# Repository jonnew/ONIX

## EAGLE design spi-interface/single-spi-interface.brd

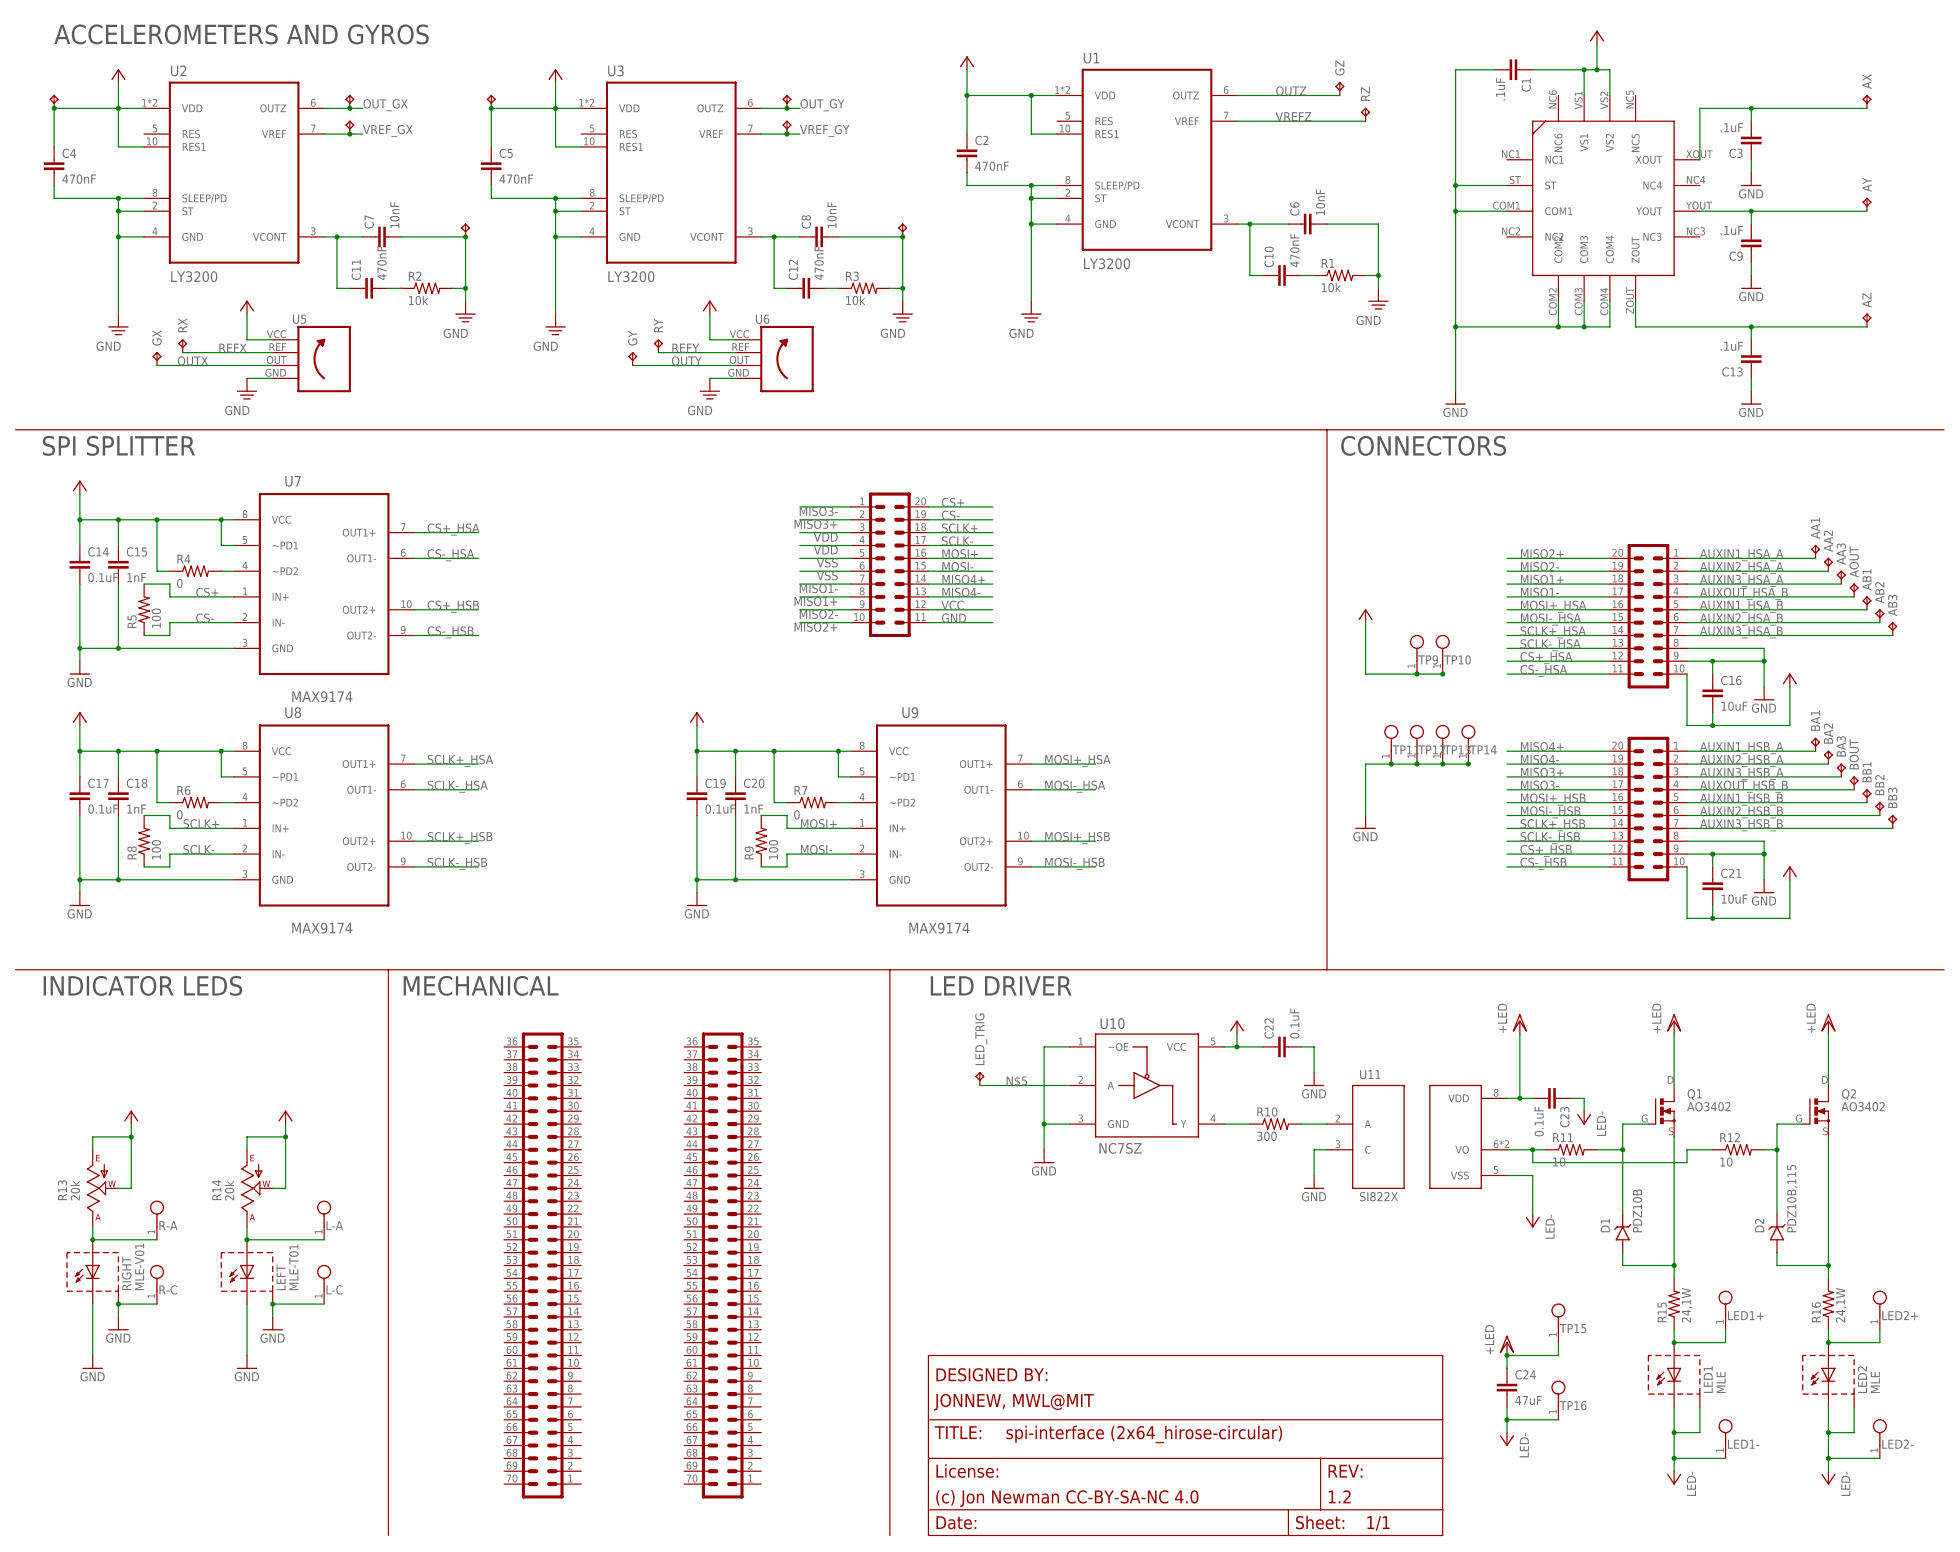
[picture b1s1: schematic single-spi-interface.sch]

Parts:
AA1, AA2, AA3: TP_0.5MM; TESTPOINT_0.5MM
AB1, AB2, AB3: TP_0.5MM; TESTPOINT_0.5MM
AOUT: TP_0.5MM; TESTPOINT_0.5MM
AX: TP_0.5MM; TESTPOINT_0.5MM
AY: TP_0.5MM; TESTPOINT_0.5MM
AZ: TP_0.5MM; TESTPOINT_0.5MM
BA1, BA2, BA3: TP_0.5MM; TESTPOINT_0.5MM
BB1, BB2, BB3: TP_0.5MM; TESTPOINT_0.5MM
BOUT: TP_0.5MM; TESTPOINT_0.5MM
C1: .1uF; 0402
C2, C4, C5, C10, C11, C12: 470nF; 0201
C3, C9, C13: .1uF; 0201
C6, C7, C8: 10nF; 0201
C14, C17, C19, C22, C23: 0.1uF; 0402
C15, C18, C20: 1nF; 0201
C16, C21: 10uF; 0805
C24: 47uF; 1206
D1: PDZ10B; SOD-323
D2: PDZ10B,115; SOD-323
DIO_HSA: PINHD-2X10_DF40-20REC; DF40-20REC
DIO_HSB: PINHD-2X10_DF40-20REC; DF40-20REC
GX: TP_0.5MM; TESTPOINT_0.5MM
GY: TP_0.5MM; TESTPOINT_0.5MM
GZ: TP_0.5MM; TESTPOINT_0.5MM
L-A: TESTPOINT_SMALL
L-C: TESTPOINT_SMALL
LED1, LED2: MLE; LED-MLE
LED1+, LED1-, LED2+, LED2-: TESTPOINT_SMALL
LED_TRIG: TP_0.5MM; TESTPOINT_0.5MM
LEFT: MLE-T01; LED-MLE
MECH_E0B: PINHD-2X35_DF40REC; DF40-70REC
MECH_W0B: PINHD-2X35_DF40REC; DF40-70REC
Q1, Q2: AO3402; SOT23-GSD
R1, R2, R3: 10k; 0201
R4, R6, R7: 0; 0201
R5, R8, R9: 100; 0201
R10: 300; 0402
R11, R12: 10; 0402
R13, R14: 20k; SM-42/43W
R15, R16: 24,1W; 0805
R-A: TESTPOINT_SMALL
R-C: TESTPOINT_SMALL
RIGHT: MLE-V01; LED-MLE
RX: TP_0.5MM; TESTPOINT_0.5MM
RY: TP_0.5MM; TESTPOINT_0.5MM
RZ: TP_0.5MM; TESTPOINT_0.5MM
TETHER: T1M-10-T-DV
TP1, TP2, TP3, TP4, TP5, TP6, TP7, TP8: TPTP08SQ; TP08SQ
TP9, TP10, TP11, TP12, TP13, TP14, TP15, TP16: TESTPOINT_SMALL
U1, U2, U3: LY3200; LGA-10-COMPACT
U4: ADXL335
U5, U6: LY3200-VERT-MODULE
U7, U8, U9: MAX9174; 10-UMAX
U10: NC7SZ; SOT-23-5
U11: SI822X; SOIC127P500X400-8N

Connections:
AUXIN1_HSA_A: AA1.1, DIO_HSA.1
AUXIN1_HSA_B: AB1.1, DIO_HSA.5
AUXIN1_HSB_A: BA1.1, DIO_HSB.1
AUXIN1_HSB_B: BB1.1, DIO_HSB.5
AUXIN2_HSA_A: AA2.1, DIO_HSA.2
AUXIN2_HSA_B: AB2.1, DIO_HSA.6
AUXIN2_HSB_A: BA2.1, DIO_HSB.2
AUXIN2_HSB_B: BB2.1, DIO_HSB.6
AUXIN3_HSA_A: AA3.1, DIO_HSA.3
AUXIN3_HSA_B: AB3.1, DIO_HSA.7
AUXIN3_HSB_A: BA3.1, DIO_HSB.3
AUXIN3_HSB_B: BB3.1, DIO_HSB.7
AUXOUT_HSA_B: AOUT.1, DIO_HSA.4
AUXOUT_HSB_B: BOUT.1, DIO_HSB.4
CS+: R5.2, TETHER.20, U7.1 (IN+)
CS+_HSA: DIO_HSA.12, U7.7 (OUT1+)
CS+_HSB: DIO_HSB.12, U7.10 (OUT2+)
CS-: R5.1, TETHER.19, U7.2 (IN-)
CS-_HSA: DIO_HSA.11, U7.6 (OUT1-)
CS-_HSB: DIO_HSB.11, U7.9 (OUT2-)
GND: C1.2, C2.2, C3.1, C4.2, C5.2, C6.2, C7.2, C8.2, C9.1, C13.1, C14.2, C15.2, C16.1, C17.2, C18.2, C19.2, C20.2, C21.1, C22.2, DIO_HSA.8, DIO_HSA.9, DIO_HSB.8, DIO_HSB.9, L-C.1, LEFT.C1 (C), LEFT.C2 (C), LEFT.HS (BODY), R1.2, R2.2, R3.2, R-C.1, RIGHT.C1 (C), RIGHT.C2 (C), RIGHT.HS (BODY), TETHER.11, TP7.TP, TP8.TP, TP11.1, TP12.1, TP13.1, TP14.1, U1.2 (ST), U1.4 (GND), U1.8 (SLEEP/PD), U2.2 (ST), U2.4 (GND), U2.8 (SLEEP/PD), U3.2 (ST), U3.4 (GND), U3.8 (SLEEP/PD), U4.COM1, U4.COM2, U4.COM3, U4.COM4, U4.ST, U5.GND, U6.GND, U7.3 (GND), U8.3 (GND), U9.3 (GND), U10.1 (~OE), U10.3 (GND), U11.3 (C)
MISO1+: DIO_HSA.18, TETHER.8
MISO1-: DIO_HSA.17, TETHER.7
MISO2+: DIO_HSA.20, TETHER.10
MISO2-: DIO_HSA.19, TETHER.9
MISO3+: DIO_HSB.18, TETHER.2
MISO3-: DIO_HSB.17, TETHER.1
MISO4+: DIO_HSB.20, TETHER.14
MISO4-: DIO_HSB.19, TETHER.13
MOSI+: R9.2, TETHER.16, U9.1 (IN+)
MOSI+_HSA: DIO_HSA.16, U9.7 (OUT1+)
MOSI+_HSB: DIO_HSB.16, U9.10 (OUT2+)
MOSI-: R9.1, TETHER.15, U9.2 (IN-)
MOSI-_HSA: DIO_HSA.15, U9.6 (OUT1-)
MOSI-_HSB: DIO_HSB.15, U9.9 (OUT2-)
unnamed: R10.2, U11.2 (A)
unnamed: C7.1, C11.1, U2.3 (VCONT)
unnamed: LED1.A1 (A), LED1.A2 (A), LED1+.1, R15.1
unnamed: D1.A, Q1.S, R15.2
unnamed: LED_TRIG.1, U10.2 (A)
unnamed: R10.1, U10.4 (Y)
unnamed: D2.C, Q2.G, R12.2
unnamed: C11.2, R2.1
unnamed: R13.1 (A), R-A.1, RIGHT.A1 (A), RIGHT.A2 (A)
unnamed: C8.1, C12.1, U3.3 (VCONT)
unnamed: D2.A, Q2.S, R16.2
unnamed: LED2.A1 (A), LED2.A2 (A), LED2+.1, R16.1
unnamed: L-A.1, LEFT.A1 (A), LEFT.A2 (A), R14.1 (A)
unnamed: C12.2, R3.1
unnamed: C6.1, C10.1, U1.3 (VCONT)
unnamed: C10.2, R1.1
unnamed: R4.2, U7.4 (~PD2)
unnamed: R7.2, U9.4 (~PD2)
unnamed: R6.2, U8.4 (~PD2)
unnamed: D1.C, Q1.G, R11.2
unnamed: R11.1, R12.1, U11.6 (VO), U11.7 (VO)
OUTX: GX.1, U5.OUT
OUTY: GY.1, U6.OUT
OUTZ: GZ.1, U1.6 (OUTZ)
OUT_GX: TP2.TP, U2.6 (OUTZ)
OUT_GY: TP4.TP, U3.6 (OUTZ)
REFX: RX.1, U5.REF
REFY: RY.1, U6.REF
SCLK+: R8.2, TETHER.18, U8.1 (IN+)
SCLK+_HSA: DIO_HSA.14, U8.7 (OUT1+)
SCLK+_HSB: DIO_HSB.14, U8.10 (OUT2+)
SCLK-: R8.1, TETHER.17, U8.2 (IN-)
SCLK-_HSA: DIO_HSA.13, U8.6 (OUT1-)
SCLK-_HSB: DIO_HSB.13, U8.9 (OUT2-)
VCC: C1.1, C2.1, C4.1, C5.1, C14.1, C15.1, C16.2, C17.1, C18.1, C19.1, C20.1, C21.2, C22.1, DIO_HSA.10, DIO_HSB.10, R4.1, R6.1, R7.1, R13.2 (W), R13.3 (E), R14.2 (W), R14.3 (E), TETHER.12, TP1.TP, TP3.TP, TP9.1, TP10.1, U1.1 (VDD), U1.9 (VDD), U1.10 (RES1), U2.1 (VDD), U2.9 (VDD), U2.10 (RES1), U3.1 (VDD), U3.9 (VDD), U3.10 (RES1), U4.VS1, U4.VS2, U5.VCC, U6.VCC, U7.5 (~PD1), U7.8 (VCC), U8.5 (~PD1), U8.8 (VCC), U9.5 (~PD1), U9.8 (VCC), U10.5 (VCC)
VDD: C23.2, C24.1, Q1.D, Q2.D, TETHER.3, TETHER.4, TP15.1, U11.8 (VDD)
VREFZ: RZ.1, U1.7 (VREF)
VREF_GX: TP5.TP, U2.7 (VREF)
VREF_GY: TP6.TP, U3.7 (VREF)
VSS: C23.1, C24.2, LED1.C1 (C), LED1.C2 (C), LED1.HS (BODY), LED1-.1, LED2.C1 (C), LED2.C2 (C), LED2.HS (BODY), LED2-.1, TETHER.5, TETHER.6, TP16.1, U11.5 (VSS)
XOUT1: AX.1, C3.2, U4.XOUT
YOUT1: AY.1, C9.2, U4.YOUT
ZOUT1: AZ.1, C13.2, U4.ZOUT

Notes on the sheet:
SPI SPLITTER
MECHANICAL
LED DRIVER
CONNECTORS
INDICATOR LEDS
ACCELEROMETERS AND GYROS

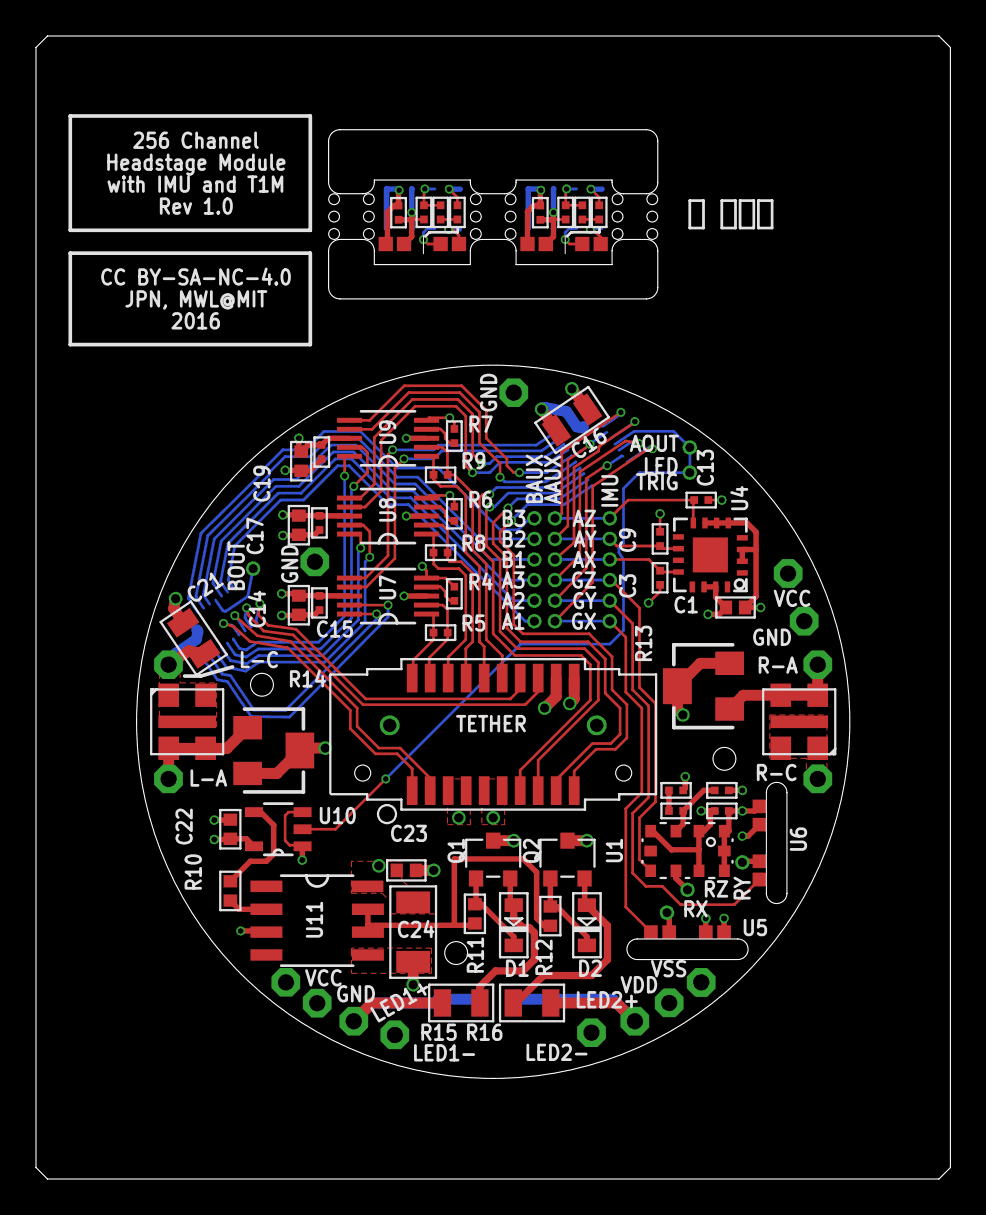
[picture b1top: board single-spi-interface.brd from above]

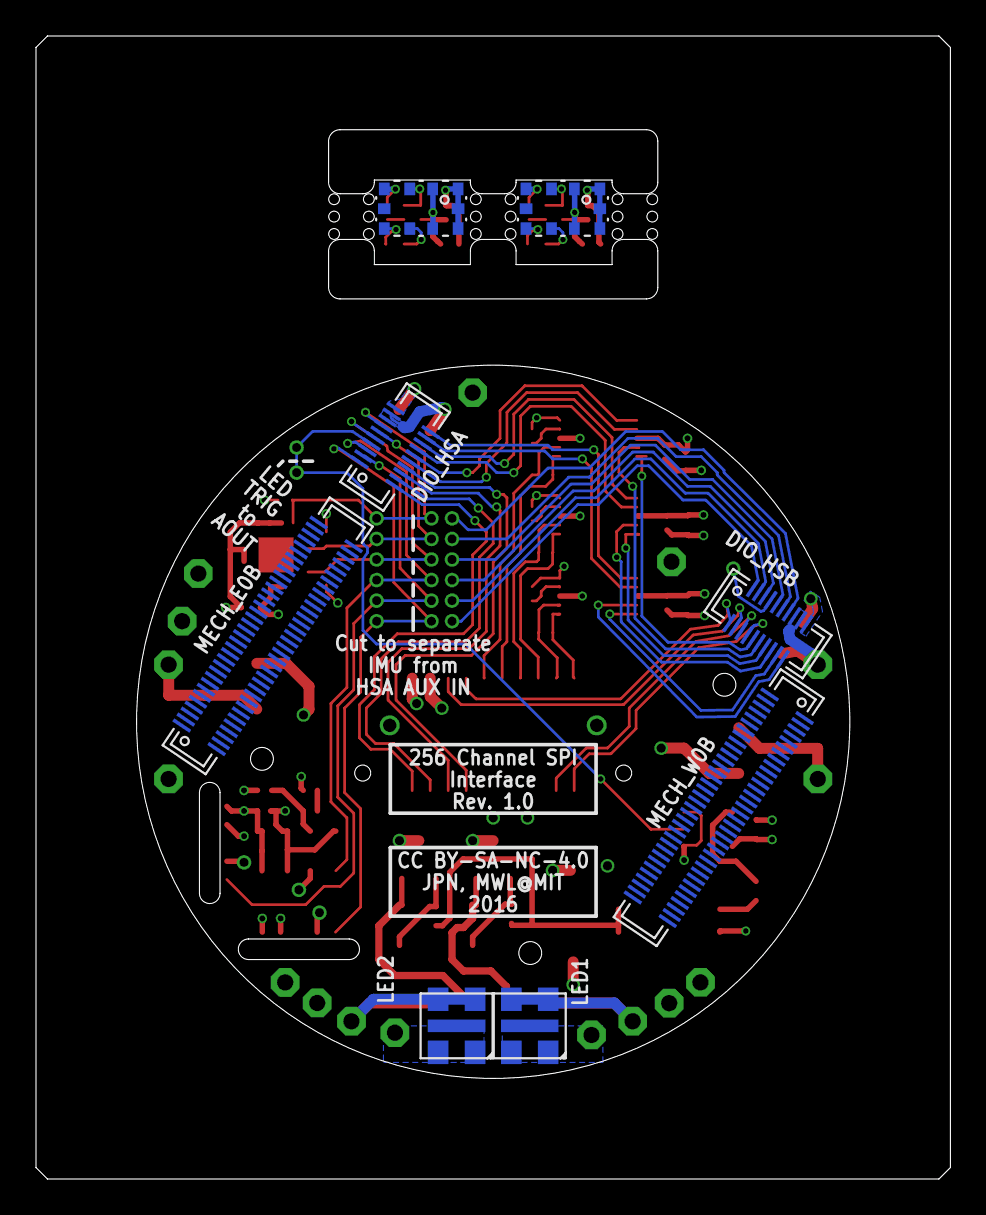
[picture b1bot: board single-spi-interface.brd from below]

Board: 4 copper layers, 50.8 x 63.5 mm, 112 parts (8 on the bottom side), 78 nets.

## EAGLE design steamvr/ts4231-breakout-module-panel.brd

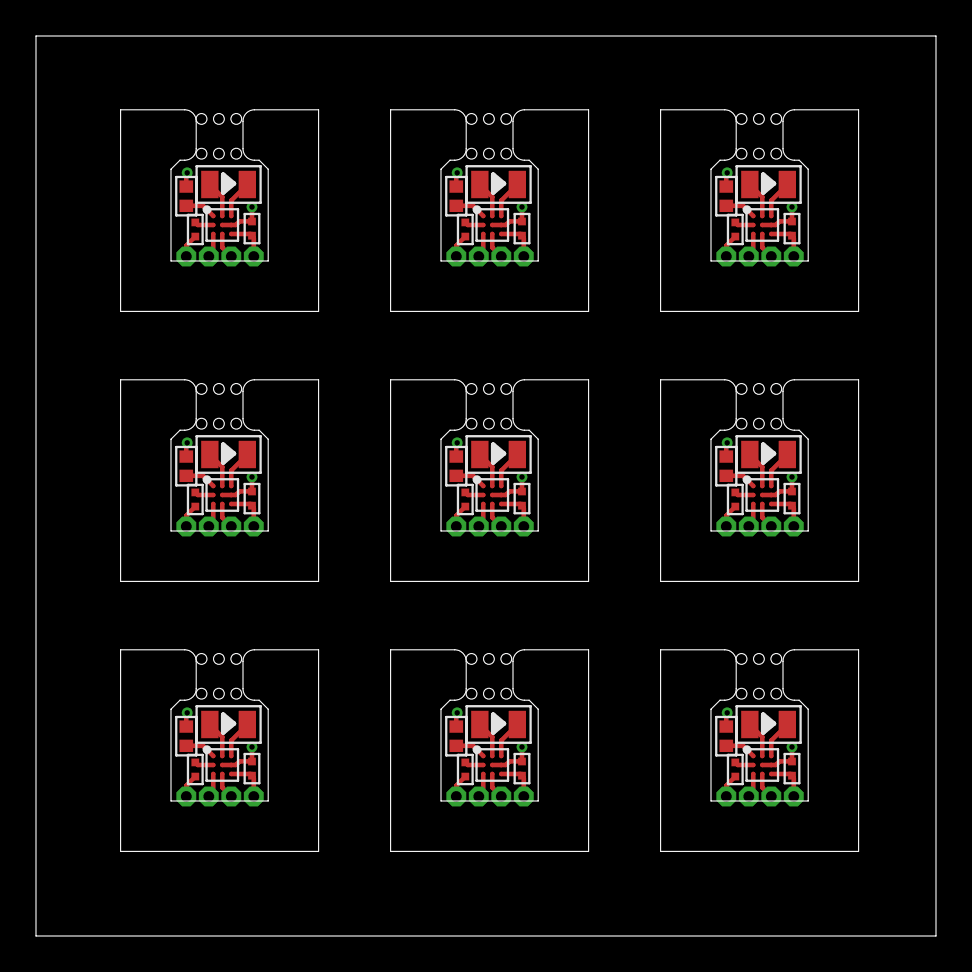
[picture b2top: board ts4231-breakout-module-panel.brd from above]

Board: 2 copper layers, 50.0 x 50.0 mm, 81 parts (0 on the bottom side), 72 nets.

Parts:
C1, C3, C5, C7, C9, C11, C13, C15, C17: 1uF; 0402
C2, C4, C6, C8, C10, C12, C14, C16, C18: 0.1uF; 0201
D, D3, D5, D7, D9, D11, D13, D15, D17: TP23MIL
D1, D2, D4, D6, D8, D10, D12, D14, D16: 0805
E, E1, E2, E3, E4, E5, E6, E7, E8: TP23MIL
GND, GND1, GND2, GND3, GND4, GND5, GND6, GND7, GND8: TP23MIL
R1, R2, R3, R4, R5, R6, R7, R8, R9: 15k; 0201
U1, U2, U3, U4, U5, U6, U7, U8, U9: TS4231; WLCSP3X3
VDD, VDD1, VDD2, VDD3, VDD4, VDD5, VDD6, VDD7, VDD8: TP23MIL

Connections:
GND: C1.2, C2.2, GND.P$1, R1.1, U1.B2, U1.B3
GND1: C3.2, C4.2, GND1.P$1, R2.1, U2.B2, U2.B3
GND2: C5.2, C6.2, GND2.P$1, R3.1, U3.B2, U3.B3
GND3: C7.2, C8.2, GND3.P$1, R4.1, U4.B2, U4.B3
GND4: C9.2, C10.2, GND4.P$1, R5.1, U5.B2, U5.B3
GND5: C11.2, C12.2, GND5.P$1, R6.1, U6.B2, U6.B3
GND6: C13.2, C14.2, GND6.P$1, R7.1, U7.B2, U7.B3
GND7: C15.2, C16.2, GND7.P$1, R8.1, U8.B2, U8.B3
GND8: C17.2, C18.2, GND8.P$1, R9.1, U9.B2, U9.B3
unnamed: D.P$1, U1.C1
unnamed: E.P$1, U1.C2
unnamed: D3.P$1, U2.C1
unnamed: D1.2, U1.A3
unnamed: D1.1, U1.A2
unnamed: R1.2, U1.B1
unnamed: C1.1, U1.A1
unnamed: E1.P$1, U2.C2
unnamed: D2.2, U2.A3
unnamed: D2.1, U2.A2
unnamed: R2.2, U2.B1
unnamed: C3.1, U2.A1
unnamed: D5.P$1, U3.C1
unnamed: E2.P$1, U3.C2
unnamed: D4.2, U3.A3
unnamed: D4.1, U3.A2
unnamed: R3.2, U3.B1
unnamed: C5.1, U3.A1
unnamed: D7.P$1, U4.C1
unnamed: E3.P$1, U4.C2
unnamed: D6.2, U4.A3
unnamed: D6.1, U4.A2
unnamed: R4.2, U4.B1
unnamed: C7.1, U4.A1
unnamed: D9.P$1, U5.C1
unnamed: E4.P$1, U5.C2
unnamed: D8.2, U5.A3
unnamed: D8.1, U5.A2
unnamed: R5.2, U5.B1
unnamed: C9.1, U5.A1
unnamed: D11.P$1, U6.C1
unnamed: E5.P$1, U6.C2
unnamed: D10.2, U6.A3
unnamed: D10.1, U6.A2
unnamed: R6.2, U6.B1
unnamed: C11.1, U6.A1
unnamed: D13.P$1, U7.C1
unnamed: E6.P$1, U7.C2
unnamed: D12.2, U7.A3
unnamed: D12.1, U7.A2
unnamed: R7.2, U7.B1
unnamed: C13.1, U7.A1
unnamed: D15.P$1, U8.C1
unnamed: E7.P$1, U8.C2
unnamed: D14.2, U8.A3
unnamed: D14.1, U8.A2
unnamed: R8.2, U8.B1
unnamed: C15.1, U8.A1
unnamed: D17.P$1, U9.C1
unnamed: E8.P$1, U9.C2
unnamed: D16.2, U9.A3
unnamed: D16.1, U9.A2
unnamed: R9.2, U9.B1
unnamed: C17.1, U9.A1
VDD: C2.1, U1.C3, VDD.P$1
VDD1: C4.1, U2.C3, VDD1.P$1
VDD2: C6.1, U3.C3, VDD2.P$1
VDD3: C8.1, U4.C3, VDD3.P$1
VDD4: C10.1, U5.C3, VDD4.P$1
VDD5: C12.1, U6.C3, VDD5.P$1
VDD6: C14.1, U7.C3, VDD6.P$1
VDD7: C16.1, U8.C3, VDD7.P$1
VDD8: C18.1, U9.C3, VDD8.P$1

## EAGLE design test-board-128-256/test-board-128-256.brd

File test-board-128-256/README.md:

# test-board-128-256
Test board for [headstage-256](../headstage-256). Allows injecting simulated
biopotentials into headstage modules via a selectable passive attenuator.
Provides LEDs and simulated electrical loads for optical and electrical
stimulation.

## Gerber Files
{% include gerber_layers.md %}

## Bill of Materials
The BOM is located on [this google
sheet](https://docs.google.com/spreadsheets/d/1F-KWcdvH_63iXjZf0cgCfDiFX6XXW3qw6rlR8DZrFpQ/edit#gid=1193719109)

## Pinout
The EIB pinout (ADC input mapping, stimulation connections, etc) is located on
[this google
sheet](https://docs.google.com/spreadsheets/d/11wRDYOqHN5lPb03yUdfXfK0zvaDYsVetplaNK-R90Gg/edit#gid=663991061)

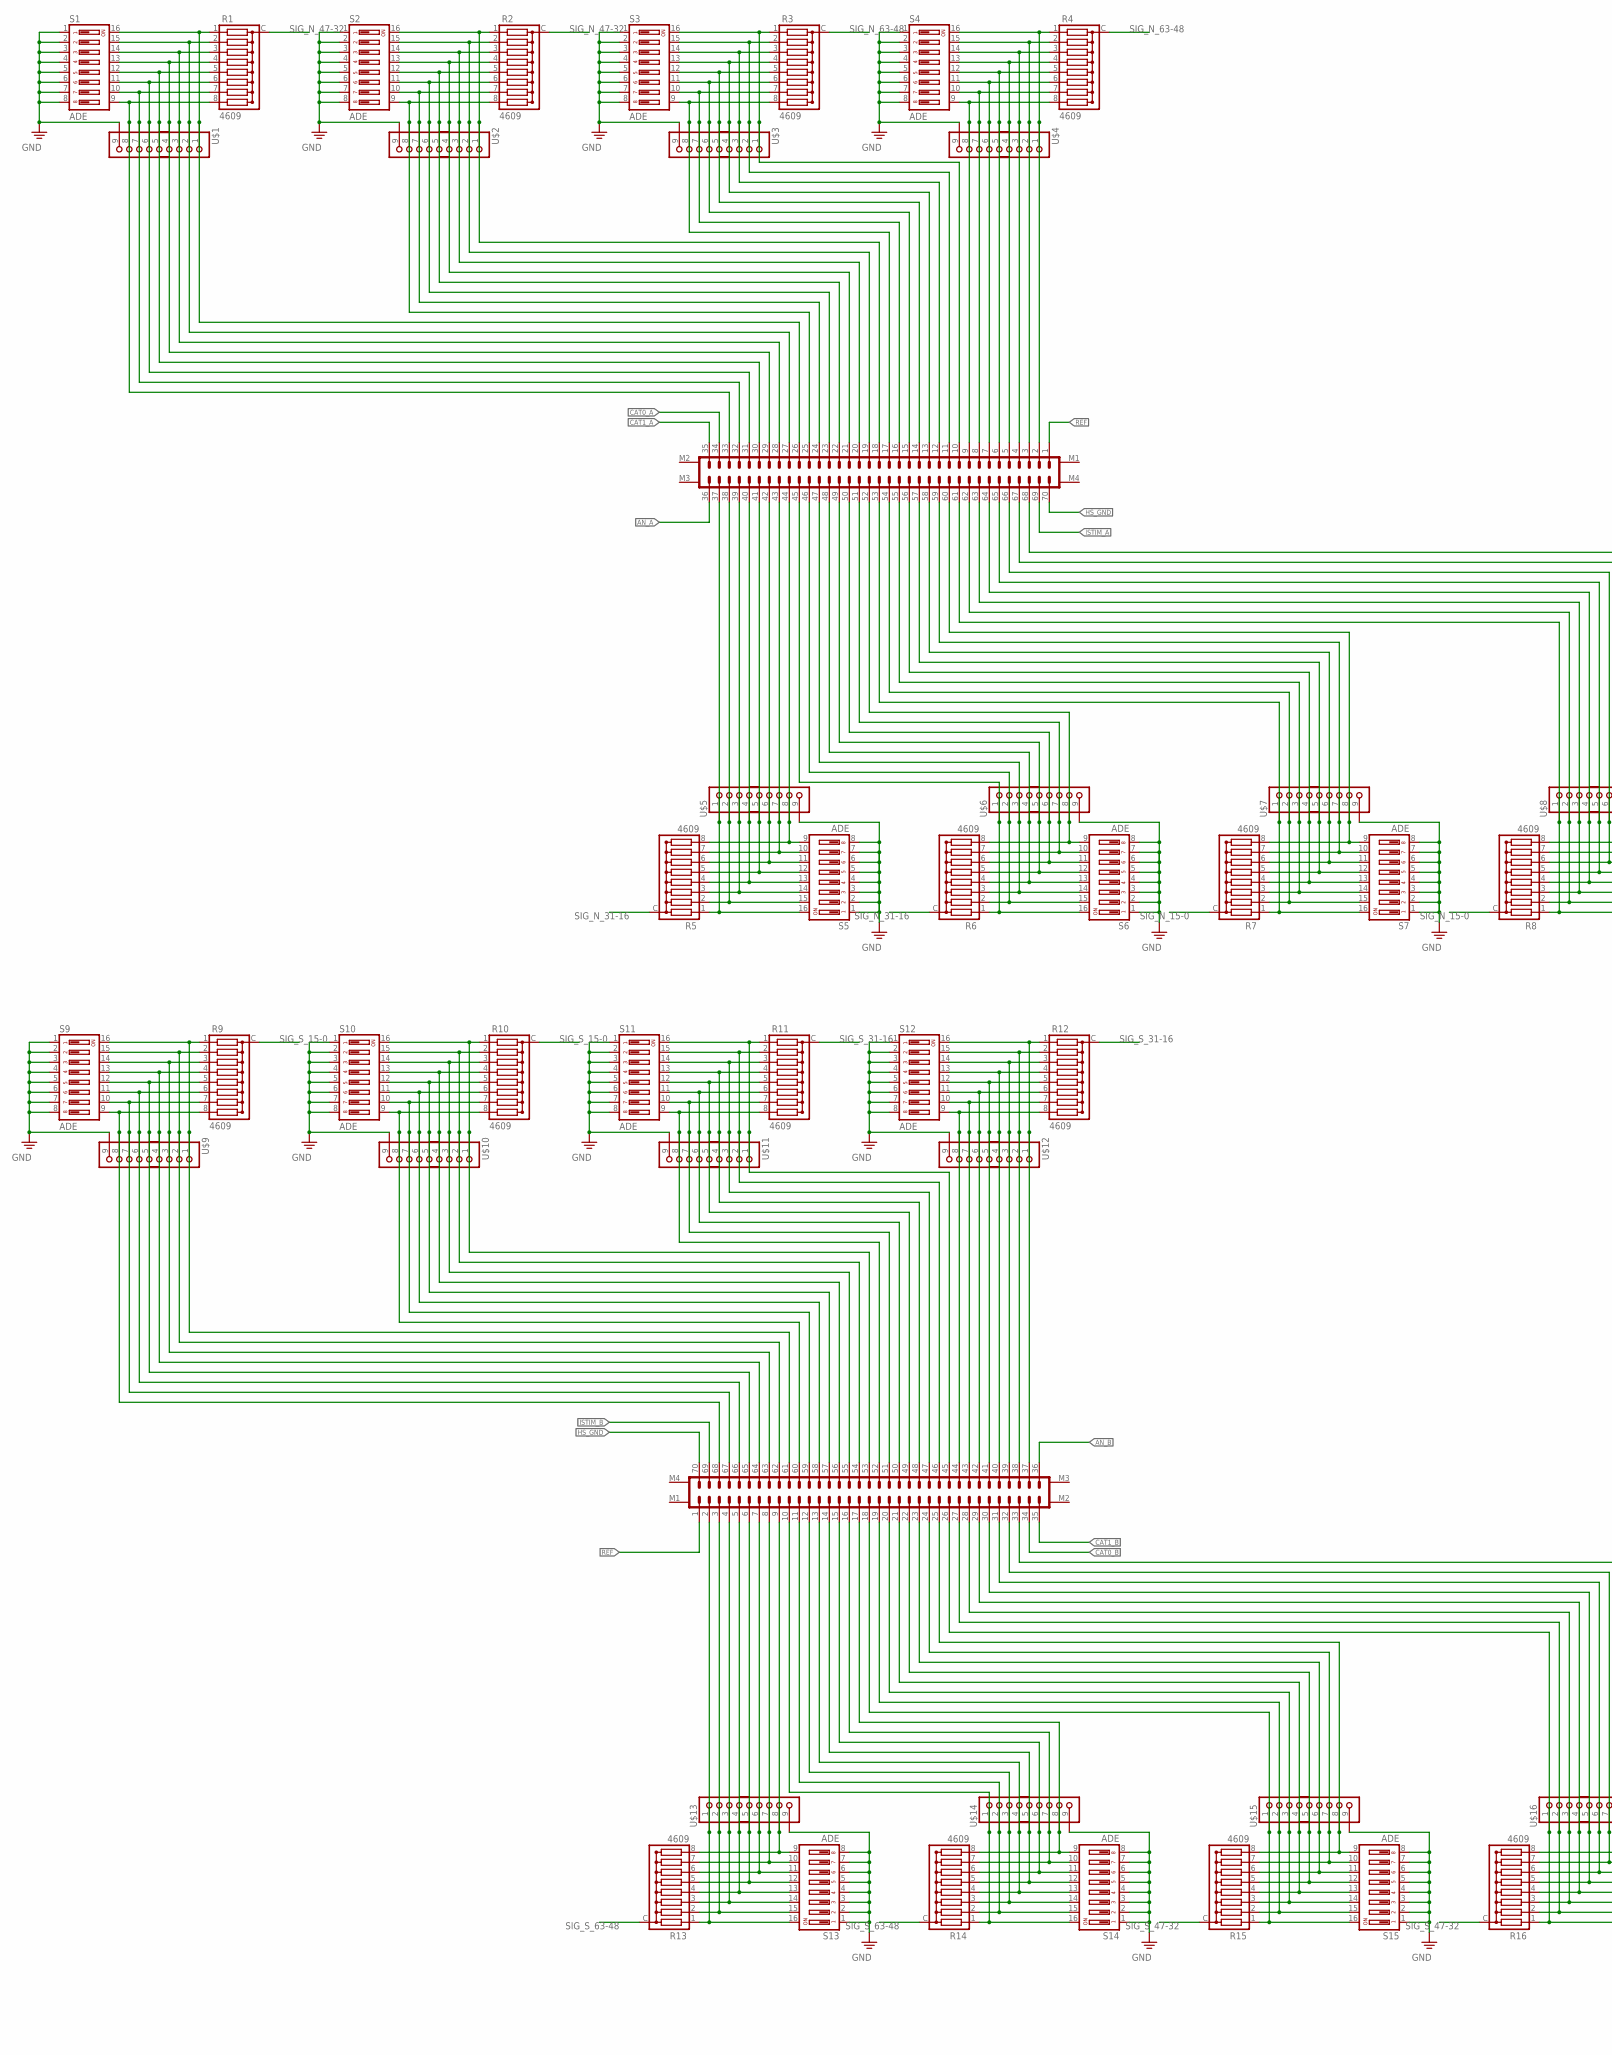
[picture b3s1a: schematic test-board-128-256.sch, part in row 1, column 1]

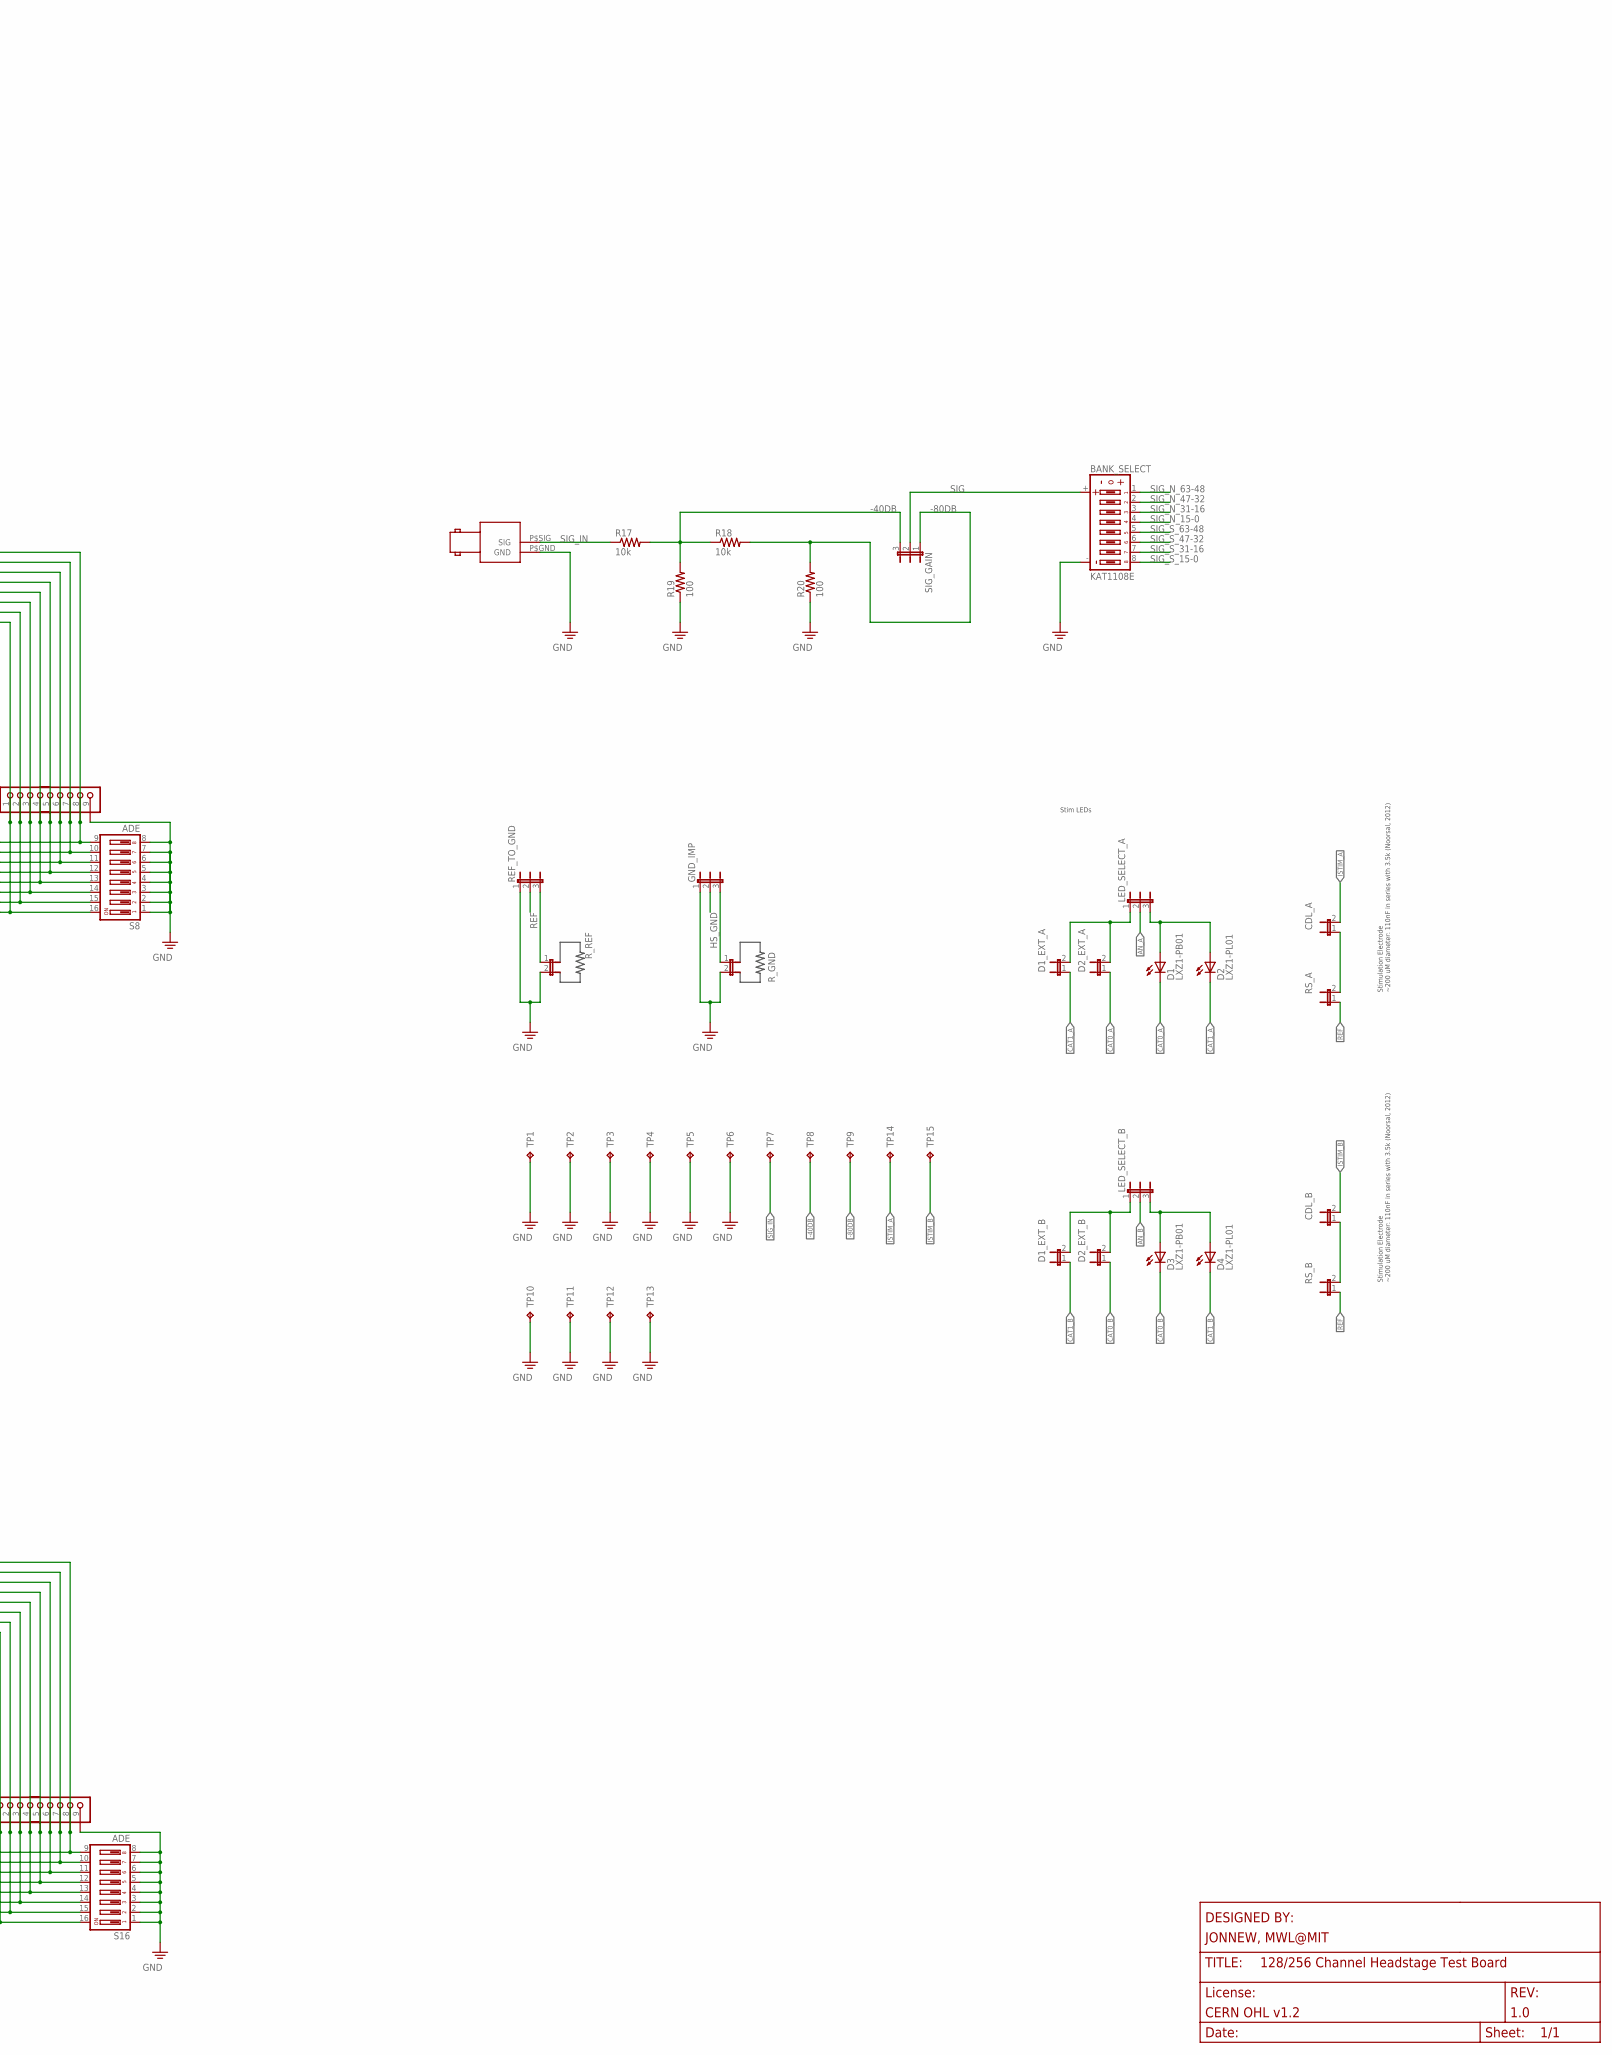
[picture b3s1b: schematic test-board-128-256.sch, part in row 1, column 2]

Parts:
A-OR-D: DF40HEAD; DF40-70HEAD
B-OR-C: DF40HEAD; DF40-70HEAD
BANK_SELECT: KAT1108E; 206-124_DIP8-SPDT
CDL_A: JP2E_THRU-HOLE; JP2
CDL_B: JP2E_THRU-HOLE; JP2
D1, D3: LXZ1-PB01; LXZ1
D1_EXT_A, D1_EXT_B, D2_EXT_A, D2_EXT_B: JP2E_THRU-HOLE; JP2
D2, D4: LXZ1-PL01; LXZ1
GND_IMP: JP3E; JP3
LED_SELECT_A: JP3E; JP3
LED_SELECT_B: JP3E; JP3
R1, R2, R3, R4, R5, R6, R7, R8, R9, R10, R11, R12, R13, R14, R15, R16: 4609; RNX8-0.1
R17, R18: 10k; 0805
R19, R20: 100; 0805
REF_TO_GND: JP3E; JP3
RS_A: JP2E_THRU-HOLE; JP2
RS_B: JP2E_THRU-HOLE; JP2
R_GND: JP2E_THRU-HOLE; JP2
R_REF: JP2E_THRU-HOLE; JP2
S1, S2, S3, S4, S5, S6, S7, S8, S9, S10, S11, S12, S13, S14, S15, S16: ADE; ADE_DIP8-SPST
SIG_GAIN: JP3E; JP3
SIG_IN: 1-1634622-0; BNC_RIGHT_ANGLE
TP1, TP2, TP3, TP4, TP5, TP6: GND; P1-20
TP7: SIG_IN; P1-20
TP8: -40dB; P1-20
TP9: -80dB; P1-20
TP10, TP11, TP12, TP13: TP_4-40; 4-40_PLATED
TP14: V_ISTIM_A; P1-20
TP15: V_ISTIM_B; P1-20
U$1, U$2, U$3, U$4, U$5, U$6, U$7, U$8, U$9, U$10, U$11, U$12, U$13, U$14, U$15, U$16: PINHD-1X9; 1X09

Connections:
-40DB: R17.2, R18.1, R19.2, SIG_GAIN.3, TP8.TP
-80DB: R18.2, R20.2, SIG_GAIN.1, TP9.TP
AN_A: A-OR-D.36, LED_SELECT_A.2
AN_B: B-OR-C.36, LED_SELECT_B.2
AN_INT: D1.A, D2.A, LED_SELECT_A.3
AN_INT1: D3.A, D4.A, LED_SELECT_B.3
CAT0_A: A-OR-D.34, D1.C, D2_EXT_A.1
CAT0_B: B-OR-C.34, D2_EXT_B.1, D3.C
CAT1_A: A-OR-D.35, D1_EXT_A.1, D2.C
CAT1_B: B-OR-C.35, D1_EXT_B.1, D4.C
GND: BANK_SELECT.-, GND_IMP.1, R19.1, R20.1, REF_TO_GND.1, R_GND.2, R_REF.2, S1.1, S1.2, S1.3, S1.4, S1.5, S1.6, S1.7, S1.8, S2.1, S2.2, S2.3, S2.4, S2.5, S2.6, S2.7, S2.8, S3.1, S3.2, S3.3, S3.4, S3.5, S3.6, S3.7, S3.8, S4.1, S4.2, S4.3, S4.4, S4.5, S4.6, S4.7, S4.8, S5.1, S5.2, S5.3, S5.4, S5.5, S5.6, S5.7, S5.8, S6.1, S6.2, S6.3, S6.4, S6.5, S6.6, S6.7, S6.8, S7.1, S7.2, S7.3, S7.4, S7.5, S7.6, S7.7, S7.8, S8.1, S8.2, S8.3, S8.4, S8.5, S8.6, S8.7, S8.8, S9.1, S9.2, S9.3, S9.4, S9.5, S9.6, S9.7, S9.8, S10.1, S10.2, S10.3, S10.4, S10.5, S10.6, S10.7, S10.8, S11.1, S11.2, S11.3, S11.4, S11.5, S11.6, S11.7, S11.8, S12.1, S12.2, S12.3, S12.4, S12.5, S12.6, S12.7, S12.8, S13.1, S13.2, S13.3, S13.4, S13.5, S13.6, S13.7, S13.8, S14.1, S14.2, S14.3, S14.4, S14.5, S14.6, S14.7, S14.8, S15.1, S15.2, S15.3, S15.4, S15.5, S15.6, S15.7, S15.8, S16.1, S16.2, S16.3, S16.4, S16.5, S16.6, S16.7, S16.8, SIG_IN.P$GND (GND), TP1.TP, TP2.TP, TP3.TP, TP4.TP, TP5.TP, TP6.TP, TP10.P$1, TP11.P$1, TP12.P$1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
HS_GND: A-OR-D.70, B-OR-C.70, GND_IMP.2
ISTIM_A: A-OR-D.69, CDL_A.2, TP14.TP
ISTIM_B: B-OR-C.69, CDL_B.2, TP15.TP
unnamed: CDL_A.1, RS_A.2
unnamed: GND_IMP.3, R_GND.1
unnamed: B-OR-C.3, R13.2, S13.15, U$13.2
unnamed: B-OR-C.5, R13.4, S13.13, U$13.4
unnamed: D1_EXT_A.2, D2_EXT_A.2, LED_SELECT_A.1
unnamed: A-OR-D.17, R3.8, S3.9, U$3.8
unnamed: A-OR-D.9, R4.8, S4.9, U$4.8
unnamed: A-OR-D.15, R3.6, S3.11, U$3.6
unnamed: A-OR-D.14, R3.5, S3.12, U$3.5
unnamed: A-OR-D.3, R4.2, S4.15, U$4.2
unnamed: A-OR-D.12, R3.3, S3.14, U$3.3
unnamed: A-OR-D.4, R4.3, S4.14, U$4.3
unnamed: A-OR-D.10, R3.1, S3.16, U$3.1
unnamed: CDL_B.1, RS_B.2
unnamed: D1_EXT_B.2, D2_EXT_B.2, LED_SELECT_B.1
unnamed: A-OR-D.7, R4.6, S4.11, U$4.6
unnamed: A-OR-D.8, R4.7, S4.10, U$4.7
unnamed: A-OR-D.6, R4.5, S4.12, U$4.5
unnamed: A-OR-D.2, R4.1, S4.16, U$4.1
unnamed: A-OR-D.27, R1.2, S1.15, U$1.2
unnamed: A-OR-D.29, R1.4, S1.13, U$1.4
unnamed: A-OR-D.43, R5.7, S5.10, U$5.7
unnamed: B-OR-C.7, R13.6, S13.11, U$13.6
unnamed: A-OR-D.32, R1.7, S1.10, U$1.7
unnamed: REF_TO_GND.3, R_REF.1
unnamed: A-OR-D.30, R1.5, S1.12, U$1.5
unnamed: A-OR-D.41, R5.5, S5.12, U$5.5
unnamed: A-OR-D.28, R1.3, S1.14, U$1.3
unnamed: B-OR-C.9, R13.8, S13.9, U$13.8
unnamed: A-OR-D.39, R5.3, S5.14, U$5.3
unnamed: A-OR-D.31, R1.6, S1.11, U$1.6
unnamed: B-OR-C.10, R14.1, S14.16, U$14.1
unnamed: A-OR-D.33, R1.8, S1.9, U$1.8
unnamed: A-OR-D.37, R5.1, S5.16, U$5.1
unnamed: A-OR-D.19, R2.2, S2.15, U$2.2
unnamed: A-OR-D.52, R6.8, S6.9, U$6.8
unnamed: A-OR-D.21, R2.4, S2.13, U$2.4
unnamed: B-OR-C.11, R14.2, S14.15, U$14.2
unnamed: A-OR-D.23, R2.6, S2.11, U$2.6
unnamed: A-OR-D.24, R2.7, S2.10, U$2.7
unnamed: B-OR-C.14, R14.5, S14.12, U$14.5
unnamed: B-OR-C.15, R14.6, S14.11, U$14.6
unnamed: A-OR-D.47, R6.3, S6.14, U$6.3
unnamed: B-OR-C.16, R14.7, S14.10, U$14.7
unnamed: B-OR-C.19, R15.2, S15.15, U$15.2
unnamed: B-OR-C.20, R15.3, S15.14, U$15.3
unnamed: B-OR-C.21, R15.4, S15.13, U$15.4
unnamed: B-OR-C.22, R15.5, S15.12, U$15.5
unnamed: B-OR-C.23, R15.6, S15.11, U$15.6
unnamed: B-OR-C.24, R15.7, S15.10, U$15.7
unnamed: B-OR-C.25, R15.8, S15.9, U$15.8
unnamed: B-OR-C.26, R16.1, S16.16, U$16.1
unnamed: A-OR-D.53, R7.1, S7.16, U$7.1
unnamed: B-OR-C.27, R16.2, S16.15, U$16.2
unnamed: B-OR-C.28, R16.3, S16.14, U$16.3
unnamed: B-OR-C.29, R16.4, S16.13, U$16.4
unnamed: B-OR-C.30, R16.5, S16.12, U$16.5
unnamed: B-OR-C.31, R16.6, S16.11, U$16.6
unnamed: B-OR-C.32, R16.7, S16.10, U$16.7
unnamed: B-OR-C.33, R16.8, S16.9, U$16.8
unnamed: B-OR-C.8, R13.7, S13.10, U$13.7
unnamed: B-OR-C.6, R13.5, S13.12, U$13.5
unnamed: B-OR-C.4, R13.3, S13.14, U$13.3
unnamed: B-OR-C.2, R13.1, S13.16, U$13.1
unnamed: B-OR-C.17, R14.8, S14.9, U$14.8
unnamed: B-OR-C.12, R14.3, S14.14, U$14.3
unnamed: B-OR-C.18, R15.1, S15.16, U$15.1
unnamed: B-OR-C.61, R9.1, S9.16, U$9.1
unnamed: B-OR-C.60, R10.8, S10.9, U$10.8
unnamed: B-OR-C.57, R10.5, S10.12, U$10.5
unnamed: B-OR-C.55, R10.3, S10.14, U$10.3
unnamed: B-OR-C.53, R10.1, S10.16, U$10.1
unnamed: B-OR-C.51, R11.7, S11.10, U$11.7
unnamed: B-OR-C.48, R11.4, S11.13, U$11.4
unnamed: B-OR-C.46, R11.2, S11.15, U$11.2
unnamed: B-OR-C.40, R12.4, S12.13, U$12.4
unnamed: B-OR-C.52, R11.8, S11.9, U$11.8
unnamed: B-OR-C.50, R11.6, S11.11, U$11.6
unnamed: B-OR-C.49, R11.5, S11.12, U$11.5
unnamed: B-OR-C.47, R11.3, S11.14, U$11.3
unnamed: B-OR-C.45, R11.1, S11.16, U$11.1
unnamed: B-OR-C.67, R9.7, S9.10, U$9.7
unnamed: B-OR-C.65, R9.5, S9.12, U$9.5
unnamed: B-OR-C.63, R9.3, S9.14, U$9.3
unnamed: B-OR-C.44, R12.8, S12.9, U$12.8
unnamed: B-OR-C.38, R12.2, S12.15, U$12.2
unnamed: B-OR-C.39, R12.3, S12.14, U$12.3
unnamed: B-OR-C.42, R12.6, S12.11, U$12.6
unnamed: B-OR-C.43, R12.7, S12.10, U$12.7
unnamed: B-OR-C.41, R12.5, S12.12, U$12.5
unnamed: B-OR-C.37, R12.1, S12.16, U$12.1
unnamed: B-OR-C.64, R9.4, S9.13, U$9.4
unnamed: B-OR-C.66, R9.6, S9.11, U$9.6
unnamed: B-OR-C.68, R9.8, S9.9, U$9.8
unnamed: B-OR-C.54, R10.2, S10.15, U$10.2
unnamed: B-OR-C.56, R10.4, S10.13, U$10.4
unnamed: B-OR-C.58, R10.6, S10.11, U$10.6
unnamed: B-OR-C.59, R10.7, S10.10, U$10.7
unnamed: B-OR-C.13, R14.4, S14.13, U$14.4
unnamed: B-OR-C.62, R9.2, S9.15, U$9.2
unnamed: A-OR-D.26, R1.1, S1.16, U$1.1
unnamed: A-OR-D.25, R2.8, S2.9, U$2.8
unnamed: A-OR-D.22, R2.5, S2.12, U$2.5
unnamed: A-OR-D.20, R2.3, S2.14, U$2.3
unnamed: A-OR-D.18, R2.1, S2.16, U$2.1
unnamed: A-OR-D.16, R3.7, S3.10, U$3.7
unnamed: A-OR-D.13, R3.4, S3.13, U$3.4
unnamed: A-OR-D.11, R3.2, S3.15, U$3.2
unnamed: A-OR-D.5, R4.4, S4.13, U$4.4
unnamed: A-OR-D.38, R5.2, S5.15, U$5.2
unnamed: A-OR-D.40, R5.4, S5.13, U$5.4
unnamed: A-OR-D.42, R5.6, S5.11, U$5.6
unnamed: A-OR-D.44, R5.8, S5.9, U$5.8
unnamed: A-OR-D.45, R6.1, S6.16, U$6.1
unnamed: A-OR-D.46, R6.2, S6.15, U$6.2
unnamed: A-OR-D.48, R6.4, S6.13, U$6.4
unnamed: A-OR-D.49, R6.5, S6.12, U$6.5
unnamed: A-OR-D.50, R6.6, S6.11, U$6.6
unnamed: A-OR-D.51, R6.7, S6.10, U$6.7
unnamed: A-OR-D.54, R7.2, S7.15, U$7.2
unnamed: A-OR-D.55, R7.3, S7.14, U$7.3
unnamed: A-OR-D.56, R7.4, S7.13, U$7.4
unnamed: A-OR-D.57, R7.5, S7.12, U$7.5
unnamed: A-OR-D.58, R7.6, S7.11, U$7.6
unnamed: A-OR-D.59, R7.7, S7.10, U$7.7
unnamed: A-OR-D.60, R7.8, S7.9, U$7.8
unnamed: A-OR-D.61, R8.1, S8.16, U$8.1
unnamed: A-OR-D.62, R8.2, S8.15, U$8.2
unnamed: A-OR-D.63, R8.3, S8.14, U$8.3
unnamed: A-OR-D.64, R8.4, S8.13, U$8.4
unnamed: A-OR-D.65, R8.5, S8.12, U$8.5
unnamed: A-OR-D.66, R8.6, S8.11, U$8.6
unnamed: A-OR-D.67, R8.7, S8.10, U$8.7
unnamed: A-OR-D.68, R8.8, S8.9, U$8.8
REF: A-OR-D.1, B-OR-C.1, REF_TO_GND.2, RS_A.1, RS_B.1
SIG: BANK_SELECT.+, SIG_GAIN.2
SIG_IN: R17.1, SIG_IN.P$SIG (SIG), TP7.TP
SIG_N_15-0: BANK_SELECT.4, R7.C, R8.C
SIG_N_31-16: BANK_SELECT.3, R5.C, R6.C
SIG_N_47-32: BANK_SELECT.2, R1.C, R2.C
SIG_N_63-48: BANK_SELECT.1, R3.C, R4.C
SIG_S_15-0: BANK_SELECT.8, R9.C, R10.C
SIG_S_31-16: BANK_SELECT.7, R11.C, R12.C
SIG_S_47-32: BANK_SELECT.6, R15.C, R16.C
SIG_S_63-48: BANK_SELECT.5, R13.C, R14.C

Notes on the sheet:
Stimulation Electrode ~200 uM diameter: 110nF in series with 3.5k (Noorsal, 2012)
Stim LEDs

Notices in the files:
spi-interface/single-spi-interface.brd:
CC BY-SA-NC-4.0
spi-interface/single-spi-interface.sch:
LICENSE: (c) Jon Newman CC-BY-SA-NC 4.0
test-board-128-256/test-board-128-256.brd:
CERN OHL v1.2
test-board-128-256/test-board-128-256.sch:
LICENSE: CERN OHL v1.2
test-board-64/revisions/rev-1.2/test-board-64.sch:
LICENSE: (c) Jon Newman CERN OHL v1.2
